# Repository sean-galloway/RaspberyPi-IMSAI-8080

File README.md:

# IMSPI 8080

A smart front panel for a 10" rack, styled after the IMSAI 8080, driven by a
Raspberry Pi (running an 8080/Z80 emulator such as z80pack or SIMH) over a single
USB link. An on-panel RP2040 owns all LED refresh and switch debounce and exposes
the panel to the Pi as a small register-mapped serial peripheral.

## Why a smart panel

The naive build wires every LED and switch straight back to the Pi header with
flying leads — which does not scale past ~60 I/O and turns into a harness. Instead
the panel carries its own microcontroller and driver silicon, and the Pi talks to
it the way a CPU talks to memory-mapped I/O: write the lamp registers, read the
switch registers. This decouples the panel's real-time refresh from whatever else
the Pi is doing, moves debounce and PWM off the Pi, and keeps a single 3.3V rail
with no level shifters.

## Panel layout

Matched to the physical panel (see `docs/panel-layout.svg`):

- Left block: three rows of 8 LEDs over 8 toggles
  - row 1 — address high (A15..A8)
  - row 2 — address low  (A7..A0)
  - row 3 — data          (D7..D0)
  - 8 data toggles (latching) below
- Right block: one row of 4 status LEDs over 4 command switches (momentary)

28 LEDs, 12 switches, on a 204 mm board in a 10" rack 3U face.
Because all 16 address bits are displayed even though only 8 data toggles exist,
EXAMINE looks fully authentic; address entry is byte-wise (see `docs/protocol.md`).

## Architecture

```
  Raspberry Pi 5 ── USB CDC ── RP2040 (Pico) ─┬─ SPI ──▶ 2x TLC5947  ─▶ 28 LEDs
   (emulator)                                  └─ GPIO ─▶ 2x 74HC165 ◀─ 12 switches
```

- MCU: RP2040 (Raspberry Pi Pico / Pico 2)
- LED driver: 2x TLC5947 (24ch, 12-bit PWM, constant current) daisy-chained -> 48ch, 28 used
- Switch input: 2x 74HC165 (parallel-in serial-out) daisy-chained -> 16 in, 12 used
- Link: RP2040 native USB CDC (`/dev/ttyACM0`); 4-pin UART is the wired fallback

See `docs/bom.md` for the parts list and `docs/panel-layout.md` for the bezel grid
and pitch math.

## Repo layout

```
docs/        protocol spec, BOM, panel layout + drawing, HMI mapping (panel legend spec)
firmware/    RP2040 firmware (Pico SDK, C)
host/        Python driver + examples for the Pi side
hardware/    KiCad PCB (rev5) + fab packages + placement/routing scripts
hardware/case/      canonical 3D rack case: rack_case.scad (fascia + tray + side
                    gussets fused into one print + blue frame), STLs, paddle caps — single source of
                    truth for all panel/case mechanical CAD
hardware/faceplate/ standalone 4 mm faceplate variant + fascia hole-map fab docs
```

The panel/case CAD was consolidated here from jetson-marker-turret (2026-10-10);
the turret repo no longer hosts panel files. See `TODO.md` for open items.

## Quick start

Firmware: see `firmware/README.md` (Pico SDK build -> drag `imspi8080.uf2` to the
Pico in BOOTSEL mode).

Host: see `host/README.md`.

```bash
cd host
pip install -e .
python examples/lamp_test.py /dev/ttyACM0
```

## Emulator integration

The panel is a clean memory-mapped-I/O seam. On each emulated CPU step, write the
LED frame (address bus, data bus, status flags) and consume any latched switch
events. z80pack and SIMH both expose CPU state and an I/O hook you can bridge to
`host/imspi`; `examples/panel_demo.py` drives the panel with a synthetic bus so you
can validate the hardware end-to-end before wiring the emulator.

## License

MIT — see `LICENSE`.

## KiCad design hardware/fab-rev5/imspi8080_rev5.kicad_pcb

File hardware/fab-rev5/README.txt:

IMSPI 8080 - rev5 fabrication package (ON-BOARD TOGGLES)
==========================================================

Board:  204.1 x 112.1 mm, 4-layer (SIG/GND-ish/SIG-ish/SIG - In1/In2 used
        as routed layers), FR4, 1 oz outer / 0.5 oz inner (std JLC/PCBWay 4L)
        min track 0.15 mm / min clearance 0.127 mm; via 0.6/0.3 (one 0.5/0.25
        blind pair - standard for any 4L fab)
        finish: any. No impedance requirements.

Works as-is with JLCPCB and PCBWay:
  - gerbers/  : all copper (4 layers) + mask/paste/silk + Edge.Cuts,
                Excellon drill split PTH/NPTH, .gbrjob
  - imspi8080-rev5-bom.csv (+ .xlsx): BOM, ONE ROW PER DESIGNATOR, 95 rows -
                exactly the 95 placements in the CPL, including the 12
                through-hole toggles (8x MTS-102 latching data SWD0-7,
                4x MTS-103-M momentary command SWC0-3; bushing center at the
                board-void center, Top side, rotation 0 = terminals toward
                the LED rows) and the J5 1x3 debug header (TH, top side).
                Only user-fitted parts: spare pull-ups R17/R18 (not placed).
                Upload the .csv or .xlsx at the BOM step.
  - imspi8080-rev5-cpl.csv : pick&place, 95 placements (JLCPCB columns, mm), incl. the 12 TH toggles;
                designators match the BOM 1:1. Also alone in jlcpcb-cpl/.
  - imspi8080_rev5.kicad_pcb / .kicad_pro / .kicad_sch : KiCad 8 source

WHAT'S NEW IN REV5 (vs rev4)
  - Full IMSAI-style toggle switch set ON the board: 12 SPDT toggles on
    SWPAD landing pads (36 pads), columns at 15 mm pitch directly under the
    LED rows, toggle bushings through the 12 board voids (Edge.Cuts).
    This is the "integrated switches" layout: no separate switch bracket,
    no J3/J4 harness - the panel plugs straight in.
  - Board height 112 mm (2U face) per docs/panel-layout.md.
  - 4-layer: 2-layer was attempted first (81/82 nets routed) and the last
    net (XOUT) was geometrically caged by its own neighbors; 4-layer was the
    pre-approved fallback and routed everything.

ASSEMBLY NOTES - THREE ITEMS (KiCad DRC: 0 errors, 3 documented items)
  Open-net check: kicad-cli drc does NOT report unconnected nets on this
  board (verified 2026-10-10 - no exclusions, not severity/prl gated).
  Before fab / after any edit run:  python3 check_opens.py
  It flood-fills copper (layer-aware, incl. the GND pour) and fails on any
  net that is not a single copper island, with an allow-list for the two
  assembly items below.
  1. HC_QH (U1 pin 12 -> U6 pin 9): add one 30 AWG wire, ~45 mm, at assembly.
     The pin-12 cluster admits no via; pads are both large and accessible.
  2. TLC_SCLK bridge: add one ~10 mm wire (a 0-ohm 0402 cannot span the
     gap) between the two TLC_SCLK islands, top copper:
       - U1-4 stub end: via at (124.32, 94.60)
       - chain stub:   (124.64, 102.34), via at (125.06, 102.76)
     Verified by direct copper trace 2026-10-10: island A = {U1-4 pad,
     2 tracks, via (124.32,94.60)}; island B = the U3-3 -> U4-3 chain
     (the 5.1 mm tail ending at (189.53,105.91) is a dead stub - ignore).
  3. GND pour has one isolated island pair (cosmetic; every GND pad is
     connected). Optional: one via anywhere in the pour stitches it.
  J1-A6 (USB-C duplicate D+ pad) is intentionally unconnected (plug
  parallels A6/B6; D+ routed via B6).

Gerbers regenerate with:
  kicad-cli pcb export gerbers --output gerbers/ \
    --layers "F.Cu,In1.Cu,In2.Cu,B.Cu,F.Paste,B.Paste,F.Mask,B.Mask,F.Silkscreen,B.Silkscreen,Edge.Cuts" \
    imspi8080_rev5.kicad_pcb
  kicad-cli pcb export drill --excellon-separate-th --output gerbers/ imspi8080_rev5.kicad_pcb

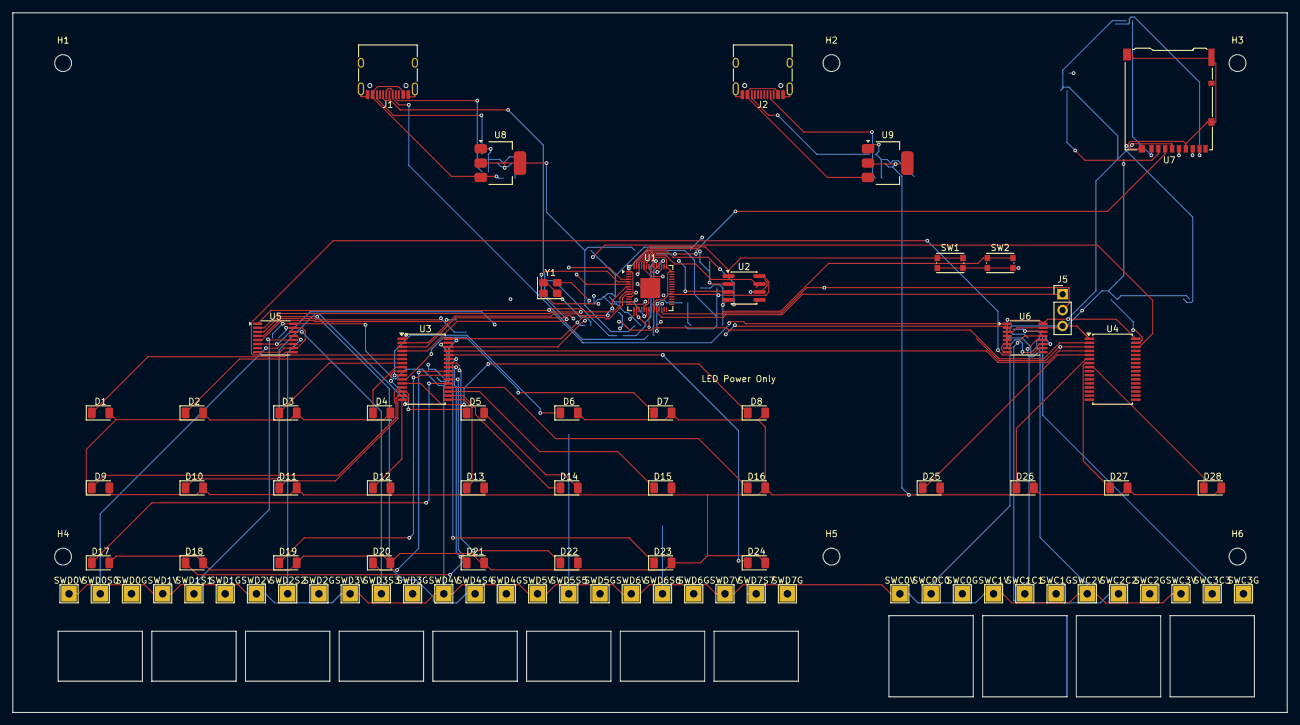
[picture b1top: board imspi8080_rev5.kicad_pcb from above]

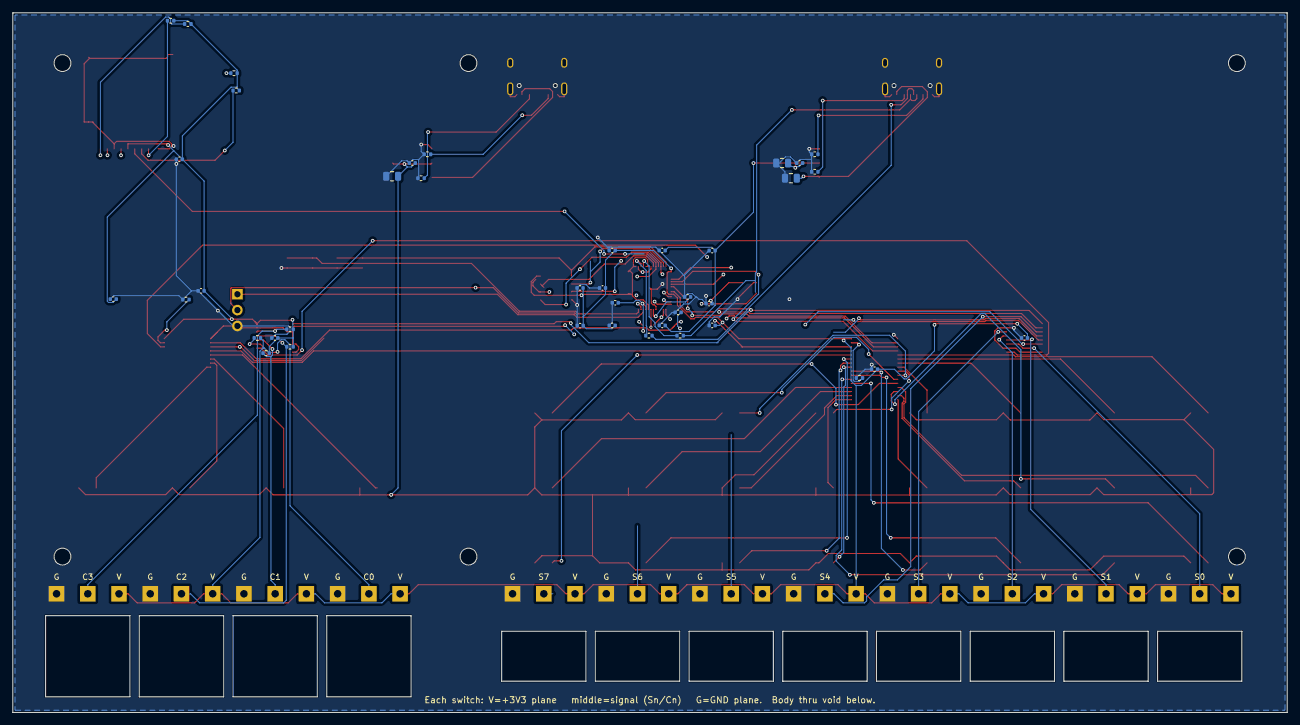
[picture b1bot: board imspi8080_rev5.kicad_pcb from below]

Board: 4 copper layers, 204.0 x 112.0 mm, 125 parts (40 on the bottom side), 82 nets.

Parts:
C1, C2, C3, C4, C5, C6, C7, C8, C9, C10, C11, C12, C13, C14, C15: 100nF; C_0402_1005Metric
C16, C17, C18, C19: 1uF; C_0402_1005Metric
C20, C21, C22: 10uF; C_0805_2012Metric
C23, C24: 15pF; C_0402_1005Metric
D1, D2, D3, D4, D5, D6, D7, D8, D9, D10, D11, D12, D13, D14, D15, D16, D17, D18, D19, D20, D21, D22, D23, D24, D25, D26, D27, D28: LED; LED_1206_3216Metric
H1, H2, H3, H4, H5, H6: MountingHole; MountingHole_2.7mm_M2.5
J1, J2: USB_C_Receptacle_USB2.0_16P; USB_C_Receptacle_HRO_TYPE-C-31-M-12
J5: Conn_01x03_Pin; PinHeader_1x03_P2.54mm_Vertical
R1, R2, R3, R4: 5.1k; R_0402_1005Metric
R5, R6: 27; R_0402_1005Metric
R7, R8: 2.4k; R_0402_1005Metric
R9, R10, R11, R12, R13, R14, R15, R16: 10k; R_0402_1005Metric
SW1, SW2: SW_Push; SW_Push_1P1T_NO_CK_KMR2
SWC0C0, SWC0G, SWC0V, SWC1C1, SWC1G, SWC1V, SWC2C2, SWC2G, SWC2V, SWC3C3, SWC3G, SWC3V: SWPAD; TestPoint_THTPad_2.5x2.5mm_Drill1.2mm
SWD0G, SWD0S0, SWD0V, SWD1G, SWD1S1, SWD1V, SWD2G, SWD2S2, SWD2V, SWD3G, SWD3S3, SWD3V, SWD4G, SWD4S4, SWD4V, SWD5G, SWD5S5, SWD5V, SWD6G, SWD6S6, SWD6V, SWD7G, SWD7S7, SWD7V: SWPAD; TestPoint_THTPad_2.5x2.5mm_Drill1.2mm
U1: RP2040; QFN-56-1EP_7x7mm_P0.4mm_EP3.2x3.2mm
U2: W25Q128JVS; SOIC-8_3.9x4.9mm_P1.27mm
U3, U4: TLC5947DAP; Texas_DAD0032A_HTSSOP-32_6.1x11mm_P0.65mm_TopEP3.71x3.81mm
U5, U6: 74HC165; TSSOP-16_4.4x5mm_P0.65mm
U7: Micro_SD_Card; microSD_HC_Hirose_DM3AT-SF-PEJM5
U8, U9: AMS1117-3.3; SOT-223-3_TabPin2
Y1: 12MHz; Crystal_SMD_3225-4Pin_3.2x2.5mm

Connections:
+3V3: C1.1, C2.1, C3.1, C4.1, C5.1, C6.1, C7.1, C8.1, C9.1, C10.1, C11.1, C12.1, C13.1, C15.1, C18.1, C19.1, C20.1, R9.1, R10.1, R11.1, R12.1, R13.1, R14.1, R15.1, R16.1, SWC0V.1, SWC1V.1, SWC2V.1, SWC3V.1, SWD0V.1, SWD1V.1, SWD2V.1, SWD3V.1, SWD4V.1, SWD5V.1, SWD6V.1, SWD7V.1, U1.1, U1.10, U1.22, U1.33, U1.42, U1.43, U1.44, U1.48, U1.49, U2.8, U3.32, U4.32, U5.16, U6.16, U7.4, U8.2
+3V3_LED: C14.1, C21.1, D1.2, D2.2, D3.2, D4.2, D5.2, D6.2, D7.2, D8.2, D9.2, D10.2, D11.2, D12.2, D13.2, D14.2, D15.2, D16.2, D17.2, D18.2, D19.2, D20.2, D21.2, D22.2, D23.2, D24.2, D25.2, D26.2, D27.2, D28.2, U9.2
CMD0: R13.2, SWC0C0.1, U6.11
CMD1: R14.2, SWC1C1.1, U6.12
CMD2: R15.2, SWC2C2.1, U6.13
CMD3: R16.2, SWC3C3.1, U6.14
GND: C1.2, C2.2, C3.2, C4.2, C5.2, C6.2, C7.2, C8.2, C9.2, C10.2, C11.2, C12.2, C13.2, C14.2, C15.2, C16.2, C17.2, C18.2, C19.2, C20.2, C21.2, C22.2, C23.2, C24.2, J1.A1, J1.A12, J1.B1, J1.B12, J1.SH, J2.A1, J2.A12, J2.B1, J2.B12, J2.SH, J5.3, R1.2, R2.2, R3.2, R4.2, R7.2, R8.2, SW1.2, SW2.2, SWC0G.1, SWC1G.1, SWC2G.1, SWC3G.1, SWD0G.1, SWD1G.1, SWD2G.1, SWD3G.1, SWD4G.1, SWD5G.1, SWD6G.1, SWD7G.1, U1.19, U1.57, U2.4, U3.1, U4.1, U5.8, U5.10, U5.15, U6.3, U6.4, U6.5, U6.6, U6.8, U6.15, U7.6, U7.SH, U8.1, U9.1, Y1.2, Y1.4
HC_CHAIN: U5.9, U6.10
HC_CLK: U1.11, U5.2, U6.2
HC_PLOAD: U1.9, U5.1, U6.1
HC_QH: U1.12, U6.9
unnamed: J5.1, U1.24
unnamed: J5.2, U1.25
unnamed: J1.A5, R1.1
unnamed: J1.B5, R2.1
unnamed: J2.A5, R3.1
unnamed: J2.B5, R4.1
unnamed: R5.2, U1.47
unnamed: R6.2, U1.46
unnamed: R7.1, U3.31
unnamed: R8.1, U4.31
unnamed: D1.1, U3.5
unnamed: D2.1, U3.6
unnamed: D3.1, U3.7
unnamed: D4.1, U3.8
unnamed: D5.1, U3.9
unnamed: D6.1, U3.10
unnamed: D7.1, U3.11
unnamed: D8.1, U3.12
unnamed: D9.1, U3.13
unnamed: D10.1, U3.14
unnamed: D11.1, U3.15
unnamed: D12.1, U3.16
unnamed: D13.1, U3.17
unnamed: D14.1, U3.18
unnamed: D15.1, U3.19
unnamed: D16.1, U3.20
unnamed: D17.1, U3.21
unnamed: D18.1, U3.22
unnamed: D19.1, U3.23
unnamed: D20.1, U3.24
unnamed: D21.1, U3.25
unnamed: D22.1, U3.26
unnamed: D23.1, U3.27
unnamed: D24.1, U3.28
unnamed: D25.1, U4.5
unnamed: D26.1, U4.6
unnamed: D27.1, U4.7
unnamed: D28.1, U4.8
unnamed: R11.2, U7.8
unnamed: R12.2, U7.1
QSPI_SCLK: U1.52, U2.6
QSPI_SD0: U1.53, U2.5
QSPI_SD1: U1.55, U2.2
QSPI_SD2: U1.54, U2.3
QSPI_SD3: U1.51, U2.7
QSPI_SS: SW1.1, U1.56, U2.1
RUN: SW2.1, U1.26
SD_CS: R9.2, U1.16, U7.2
SD_MISO: R10.2, U1.15, U7.7
SD_MOSI: U1.14, U7.3
SD_SCK: U1.13, U7.5
SW0: SWD0S0.1, U5.11
SW1: SWD1S1.1, U5.12
SW2: SWD2S2.1, U5.13
SW3: SWD3S3.1, U5.14
SW4: SWD4S4.1, U5.3
SW5: SWD5S5.1, U5.4
SW6: SWD6S6.1, U5.5
SW7: SWD7S7.1, U5.6
TLC_BLANK: U1.7, U3.2, U4.2
TLC_CHAIN: U3.29, U4.4
TLC_SCLK: U1.4, U3.3, U4.3
TLC_SIN: U1.5, U3.4
TLC_XLAT: U1.6, U3.30, U4.30
USB_DM_CONN: J1.A7, J1.B7, R6.1
USB_DP_CONN: J1.A6, J1.B6, R5.1
VBUS_LED: J2.A4, J2.A9, J2.B4, J2.B9, U9.3
VBUS_LOGIC: C22.1, J1.A4, J1.A9, J1.B4, J1.B9, U8.3
VCORE: C16.1, C17.1, U1.23, U1.45, U1.50
XIN: C23.1, U1.20, Y1.1
XOUT: C24.1, U1.21, Y1.3

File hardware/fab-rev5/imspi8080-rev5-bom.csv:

Comment,Designator,Footprint,Qty,MPN / suggested part,Notes
"RP2040",U1,"QFN-56 (7x7mm)",1,RP2040,"MCU. Copy RP2040 minimal reference design. Extended part."
"QSPI Flash 16MB",U2,SOIC-8,1,W25Q128JVSIQ,"Boot flash (firmware lives here). Basic/common."
"12MHz crystal",Y1,SMD-3225-4P,1,"12MHz 20pF","Core clock. Basic. Load caps C_Y1a/b."
"TLC5947 24ch LED driver",U3;U4,HTSSOP-32,2,TLC5947DAP,"LED drivers, daisy-chained. Extended part (1 line = both)."
"74HC165 PISO shift reg",U5;U6,TSSOP-16,2,SN74HC165PWR,"Switch inputs, daisy-chained."
"microSD socket push-pull",U7,"SMD push-pull",1,"microSD TF push-pull","Data storage (optional). Pick a JLCPCB-library SMD socket."
"AMS1117-3.3",U8,SOT-223,1,AMS1117-3.3,"3.3V logic rail from USB-C #1 VBUS. Basic."
"AMS1117-3.3",U9,SOT-223,1,AMS1117-3.3,"3.3V LED anode rail from USB-C #2 VBUS (keeps drivers cool)."
"USB-C receptacle 16P",J1,"USB-C 16P SMD",1,"TYPE-C-31-M-12","Power + data to the Pi. 2x CC resistors + 2x D series R."
"USB-C receptacle 16P",J2,"USB-C 16P SMD",1,"TYPE-C-31-M-12","Dedicated LED power only (VBUS+GND+CC). No data lines."
"Mini-toggle SPDT ON-ON (latching)",SWD0;SWD1;SWD2;SWD3;SWD4;SWD5;SWD6;SWD7,"MTS-102",8,MTS-102,"8 latching data toggles (D7..D0), board-mounted, bushing through PCB void"
Mini-toggle SPDT momentary",SWC0;SWC1;SWC2;SWC3,"MTS-103-M",4,MTS-103-M,"4 momentary command toggles, board-mounted, bushing through PCB void"
"SWD header 1x3",J5,"1x3 2.54mm",1,"header 1x3","Debug/reflash (optional). Can be pads only."
"Tactile button",SW1;SW2,"SMD tactile 4P",2,"tactile 3x4mm","SW1=BOOTSEL, SW2=RUN/reset."
"LED red 1206",D1;D2;D3;D4;D5;D6;D7;D8;D9;D10;D11;D12;D13;D14;D15;D16;D17;D18;D19;D20;D21;D22;D23;D24;D25;D26;D27;D28,LED-1206,28,"red 1206 diffused","No series resistors (TLC5947 is constant-current). Check PCBA type is not Standard-Only if you want Economic."
"5.1k",R1;R2;R3;R4,R0402,4,"5.1k 0402","USB-C CC pulldowns: 2 per connector (J1,J2)."
"27",R5;R6,R0402,2,"27R 0402","USB D+/D- series resistors (J1 data only)."
"2.4k",R7;R8,R0402,2,"2.4k 0402","TLC5947 IREF (sets per-LED current ~15mA; raise R to lower current/heat)."
"10k",R9;R10;R11;R12;R13;R14;R15;R16;R17;R18,R0402,10,"10k 0402","Pull-ups: SD CS+data (4), command-switch inputs (4), spares (2)."
"100nF",C1;C2;C3;C4;C5;C6;C7;C8;C9;C10;C11;C12;C13;C14;C15,C0402,15,"100nF 0402","Per-IC decoupling (RP2040 needs several, TLC5947 x2, 165 x2, flash, SD, regs)."
"1uF",C16;C17;C18;C19,C0402,4,"1uF 0402","RP2040 core (1.1V) decoupling + SD socket local."
"10uF",C20;C21;C22,C0805,3,"10uF 0805","Bulk on 3.3V logic, LED rail, and USB VBUS."
"15pF",C23;C24,C0402,2,"15pF 0402","Crystal load caps (tune to crystal spec)."

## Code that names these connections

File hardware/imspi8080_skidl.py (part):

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mcu['ADC_AVDD'] += v3_log      # tie to 3V3 (add ferrite in layout if you want a clean ADC)
mcu['VREG_VIN'] += v3_log      # feed the internal core LDO from 3V3
mcu['VREG_VOUT']+= vcore       # 1.1V core out
mcu['DVDD']     += vcore       # both DVDD (digital core) pins from the internal LDO
mcu['GND']      += gnd         # QFN exposed pad (pin 57)
mcu['TESTEN']   += gnd         # tie low (required)

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mcu['XIN'] += xin; mcu['XOUT'] += xout
Y1 = Part('Device', 'Crystal_GND24', ref='Y1', value='12MHz',
          footprint='Crystal:Crystal_SMD_3225-4Pin_3.2x2.5mm')
Y1[1] += xin; Y1[3] += xout; Y1['G'] += gnd   # pins 2 & 4 are the grounded case
C('C23', '15pF')[1, 2] += xin, gnd
C('C24', '15pF')[1, 2] += xout, gnd

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tlc_xlat = Net('TLC_XLAT'); tlc_blank = Net('TLC_BLANK')
hc_pload = Net('HC_PLOAD'); hc_clk = Net('HC_CLK'); hc_qh = Net('HC_QH')
sd_sck = Net('SD_SCK'); sd_mosi = Net('SD_MOSI'); sd_miso = Net('SD_MISO'); sd_cs = Net('SD_CS')
mcu['GPIO2'] += tlc_sclk; mcu['GPIO3'] += tlc_sin
mcu['GPIO4'] += tlc_xlat; mcu['GPIO5'] += tlc_blank
mcu['GPIO7'] += hc_pload; mcu['GPIO8'] += hc_clk; mcu['GPIO9'] += hc_qh
mcu['GPIO10'] += sd_sck; mcu['GPIO11'] += sd_mosi
mcu['GPIO12'] += sd_miso; mcu['GPIO13'] += sd_cs

# ---------------------------------------------------------------------------
# USB-C receptacles (J1 data+power, J2 power-only). Both TYPE-C-31-M-12 (16P).
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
